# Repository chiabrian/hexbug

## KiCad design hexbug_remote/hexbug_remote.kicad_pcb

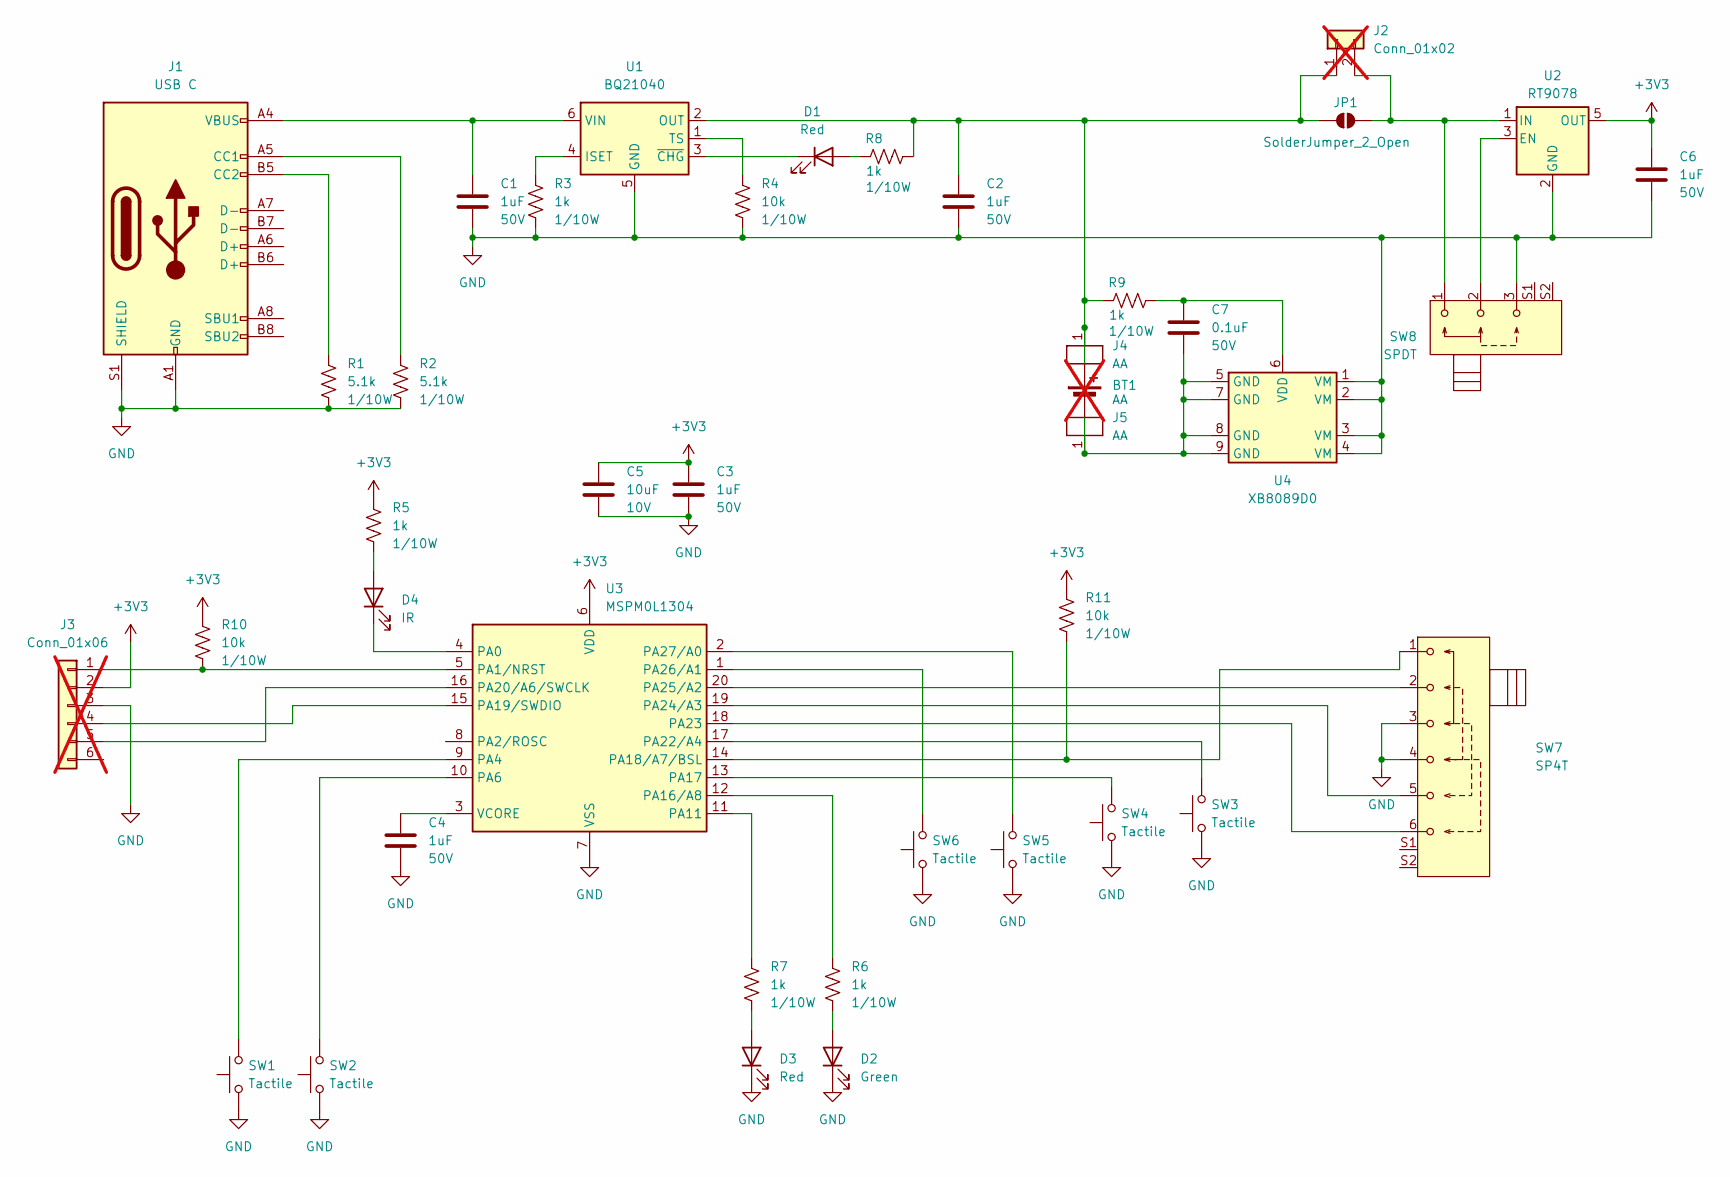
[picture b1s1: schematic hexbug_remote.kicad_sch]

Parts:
BT1: AA; Battery_Holder_MPD_BCAAPC; Manufacturer Part Numbe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 2460; LCSC Part Number C5370863; not fitted
C1, C2, C3, C4, C6: 1uF; C_0603_1608Metric; Voltage 50V; Tolerance 10%; Manufacturer Part Numbe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 CL10A105KB8NNNC; LCSC Part Number C15849
C5: 10uF; C_0603_1608Metric; Voltage 10V; Tolerance 10%; Manufacturer Part Numbe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 CL10A106KP8NNNC; LCSC Part Number C19702
C7: 0.1uF; C_0603_1608Metric; Voltage 50V; Tolerance 10%; Manufacturer Part Numbe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 CL10B104KB8NNNC; LCSC Part Number C14663
D1, D3: Red; LED_0603_1608Metric_Pad1.05x0.95mm_HandSolder; Manufacturer Part Numbe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 KT-0603R; LCSC Part Number C2286
D2: Green; LED_0603_1608Metric_Pad1.05x0.95mm_HandSolder; Manufacturer Part Numbe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 KT-0603G; LCSC Part Number C12624
D4: IR; LED_D5.0mm_Horizontal_O6.35mm_Z3.0mm; Manufacturer Part Numbe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 IR333C-A; LCSC Part Number C5130
J1: USB C; USBC_16P; Voltage 20V; Manufacturer Part Numbe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 HC-TYPE-C-16P-01A; LCSC Part Number C2894897
J2: Conn_01x02; PinHeader_1x02_P2.54mm_Vertical; not fitted
J3: Conn_01x06; PinHeader_1x06_P2.54mm_Vertical; not fitted
J4, J5: AA; Battery_Clip_Keystone_53; Manufacturer Part Numbe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 53; LCSC Part Number C5352788
JP1: SolderJumper_2_Open; SolderJumper-2_P1.3mm_Open_TrianglePad1.0x1.5mm
R1, R2: 5.1k; R_0603_1608Metric_Pad0.98x0.95mm_HandSolder; Tolerance 1%; Manufacturer Part Numbe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 RC0603FR-075K1L; LCSC Part Number C23186
R3, R5, R6, R7, R8, R9: 1k; R_0603_1608Metric_Pad0.98x0.95mm_HandSolder; Tolerance 1%; Manufacturer Part Numbe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 RC0603FR-071KL; LCSC Part Number C21190
R4, R10, R11: 10k; R_0603_1608Metric_Pad0.98x0.95mm_HandSolder; Tolerance 1%; Manufacturer Part Numbe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 RC0603FR-0710KL; LCSC Part Number C25804
SW1, SW2: Tactile; SW_Tactile_SPST_Angled_PTS645Vx58-2LFS; Voltage 12V; Manufacturer Part Numbe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 TC-6615-7-260G; LCSC Part Number C2845275
SW3, SW4, SW5, SW6: Tactile; SW_TH_Tactile_Omron_B3F-106x; Voltage 12V; Manufacturer Part Numbe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 TC-6610-7-260G; LCSC Part Number C2845253
SW7: SP4T; SW_SP4T_Slide_Samesky_SLW-147844; Voltage 50V; Manufacturer Part Numbe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 SK14D07VG4; LCSC Part Number C22435626
SW8: SPDT; SW_SPDT_Slide_CK_SK12D07VG4; Voltage 30V; Manufacturer Part Numbe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 SK12D07VG4; LCSC Part Number C22435621
U1: BQ21040; SOT-23-6; Voltage 3.5-28V; Manufacturer Part Numbe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 BQ21040DBVR; LCSC Part Number C202311
U2: RT9078; SOT-23-5; Voltage 1.2-5.5V; Manufacturer Part Numbe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 RT9078-33GJ5; LCSC Part Number C110427
U3: MSPM0L1304; TI_DGS20; Voltage 1.62-3.6V; Manufacturer Part Numbe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 MSPM0L1304TDGS20R; LCSC Part Number C22362611
U4: XB8089D0; SOP-8-1EP_3.9x4.9mm_P1.27mm_EP2.4x3.3mm; Voltage 6V; Manufacturer Part Numbe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 XB8089D0; LCSC Part Number C2760005

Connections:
+3V3: C3.1, C5.1, C6.1, J3.2, R5.1, R10.1, R11.1, U2.5 (OUT), U3.6 (VDD)
GND: C1.2, C2.2, C3.2, C4.2, C5.2, C6.2, D2.1 (K), D3.1 (K), J1.A1 (GND), J1.A12 (GND), J1.B1 (GND), J1.B12 (GND), J1.S1 (SHIELD), J3.3, R1.2, R2.2, R3.2, R4.2, SW1.1, SW2.1, SW3.1, SW4.1, SW5.1, SW6.1, SW7.3, SW7.4, SW8.3, U1.5 (GND), U2.2 (GND), U3.7 (VSS), U4.1 (VM), U4.2 (VM), U4.3 (VM), U4.4 (VM)
unnamed: BT1.1 (+), C2.1, J2.1, J4.1, JP1.1 (A), R8.1, R9.2, U1.2 (OUT)
unnamed: BT1.2 (-), C7.2, J5.1, U4.5 (GND), U4.7 (GND), U4.8 (GND), U4.9 (GND)
unnamed: D1.2 (A), R8.2
unnamed: D1.1 (K), U1.3 (~CHG)
unnamed: D2.2 (A), R6.2
unnamed: D3.2 (A), R7.2
unnamed: D4.2 (A), R5.2
unnamed: D4.1 (K), U3.4 (PA0)
unnamed: J1.A5 (CC1), R2.1
unnamed: J1.B5 (CC2), R1.1
unnamed: J2.2, JP1.2 (B), SW8.1, U2.1 (IN)
unnamed: J3.1, R10.2, U3.5 (PA1/NRST)
unnamed: J3.4, U3.15 (PA19/SWDIO)
unnamed: J3.5, U3.16 (PA20/A6/SWCLK)
unnamed: R3.1, U1.4 (ISET)
unnamed: R4.1, U1.1 (TS)
unnamed: C1.1, J1.A4 (VBUS), J1.A9 (VBUS), J1.B4 (VBUS), J1.B9 (VBUS), U1.6 (VIN)
unnamed: SW8.2, U2.3 (EN)
unnamed: SW1.2, U3.9 (PA4)
unnamed: SW2.2, U3.10 (PA6)
unnamed: R7.1, U3.11 (PA11)
unnamed: R6.1, U3.12 (PA16/A8)
unnamed: SW4.2, U3.13 (PA17)
unnamed: R11.2, SW7.1, U3.14 (PA18/A7/BSL)
unnamed: SW3.2, U3.17 (PA22/A4)
unnamed: SW7.6, U3.18 (PA23)
unnamed: SW7.5, U3.19 (PA24/A3)
unnamed: SW7.2, U3.20 (PA25/A2)
unnamed: SW6.2, U3.1 (PA26/A1)
unnamed: SW5.2, U3.2 (PA27/A0)
unnamed: C4.1, U3.3 (VCORE)
unnamed: C7.1, R9.1, U4.6 (VDD)

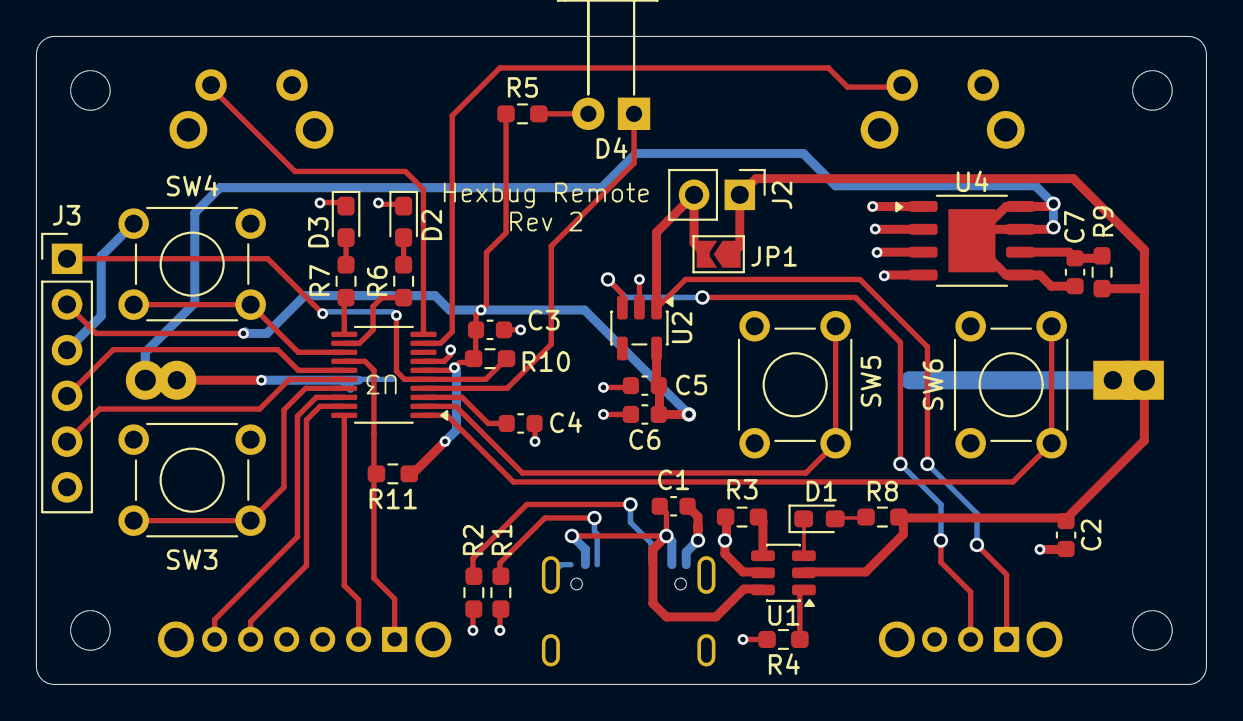
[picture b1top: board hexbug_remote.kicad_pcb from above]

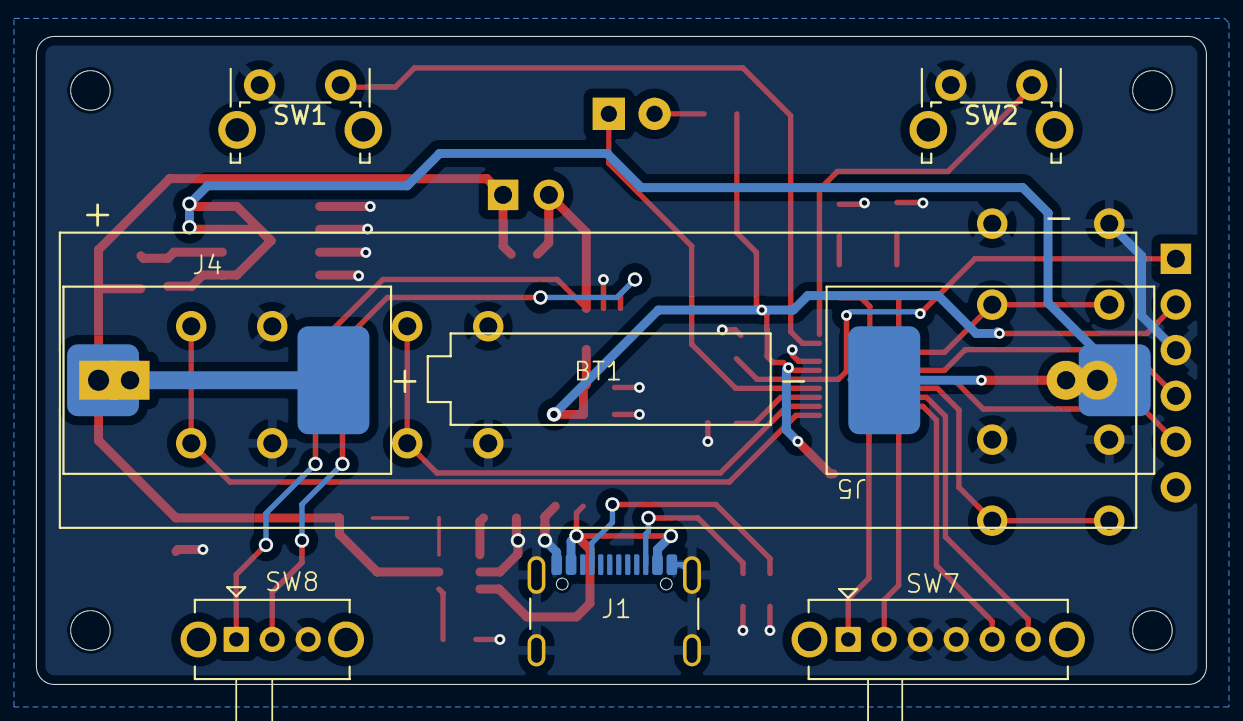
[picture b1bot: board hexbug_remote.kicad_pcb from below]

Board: 2 copper layers, 65.0 x 36.0 mm, 41 parts (8 on the bottom side), 34 nets.

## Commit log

2026-02-24 Update Enclosure
2026-03-01 Update to use local db lib
2026-03-01 Update Libraries
2026-03-02 --Add Gerber Files
2026-03-07 Add Battery Protection
2026-03-07 Update Step File
2026-03-07 Increase depth for battery clips
2026-03-29 Fix Schematic Symbol
2026-04-17 Add Firmware Update PCB to Rev 2 --Pull up resistor for reset
2026-04-17 Add Gitignore
